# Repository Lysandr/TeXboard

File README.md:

# TeXboard
I designed a mechanical keyboard from scratch for the scientists, mathematicians, and control theorists of the world. It has LaTeX bindings for math and greek.

This also works as generic keyboard matrix interpretation code. Writtenin C-arduino for the teensy 3.1/2

12/1/2018 havent quite worked out some bugs in Latex, and functions. Excuse: I have spent maybe 2 hours on software.
2/14/2018 adding support for MkII.

Todo:
FN/GRK/LTX functions still need to be implemented (imlazy)
dual keys tend to have an odd glitch, needs to be investigated
MkIII hardware --> switch over to STM32 with QMK firmware... also put extension keys on the left, gives more mouse room. Create parametric case design, which prints perfectly and makes lasercut piece easier to deal with.

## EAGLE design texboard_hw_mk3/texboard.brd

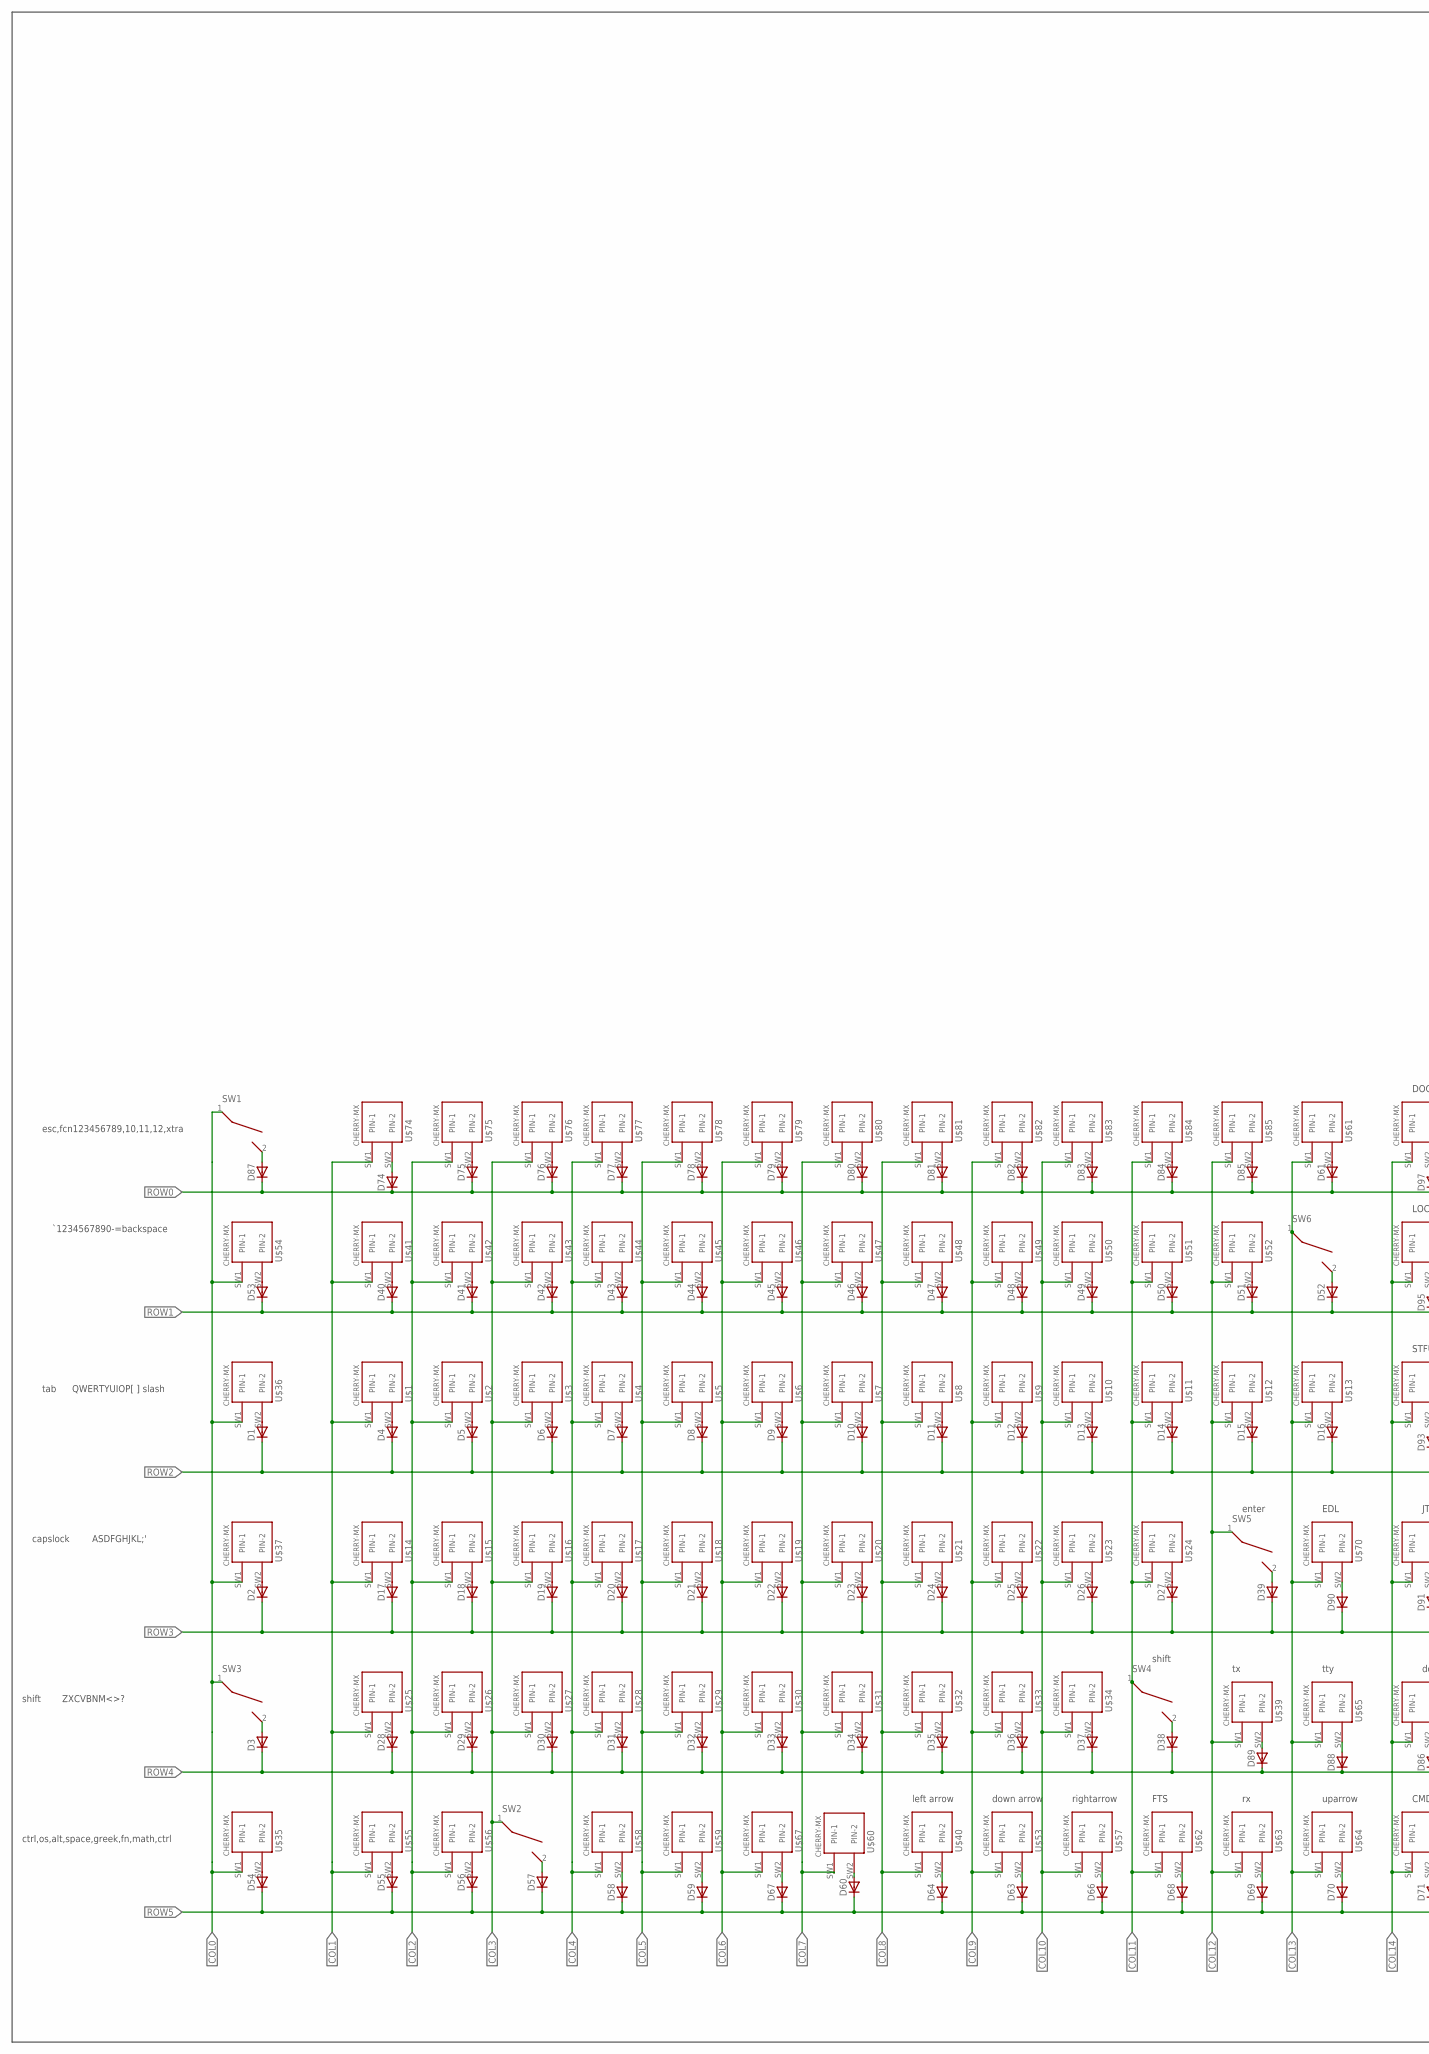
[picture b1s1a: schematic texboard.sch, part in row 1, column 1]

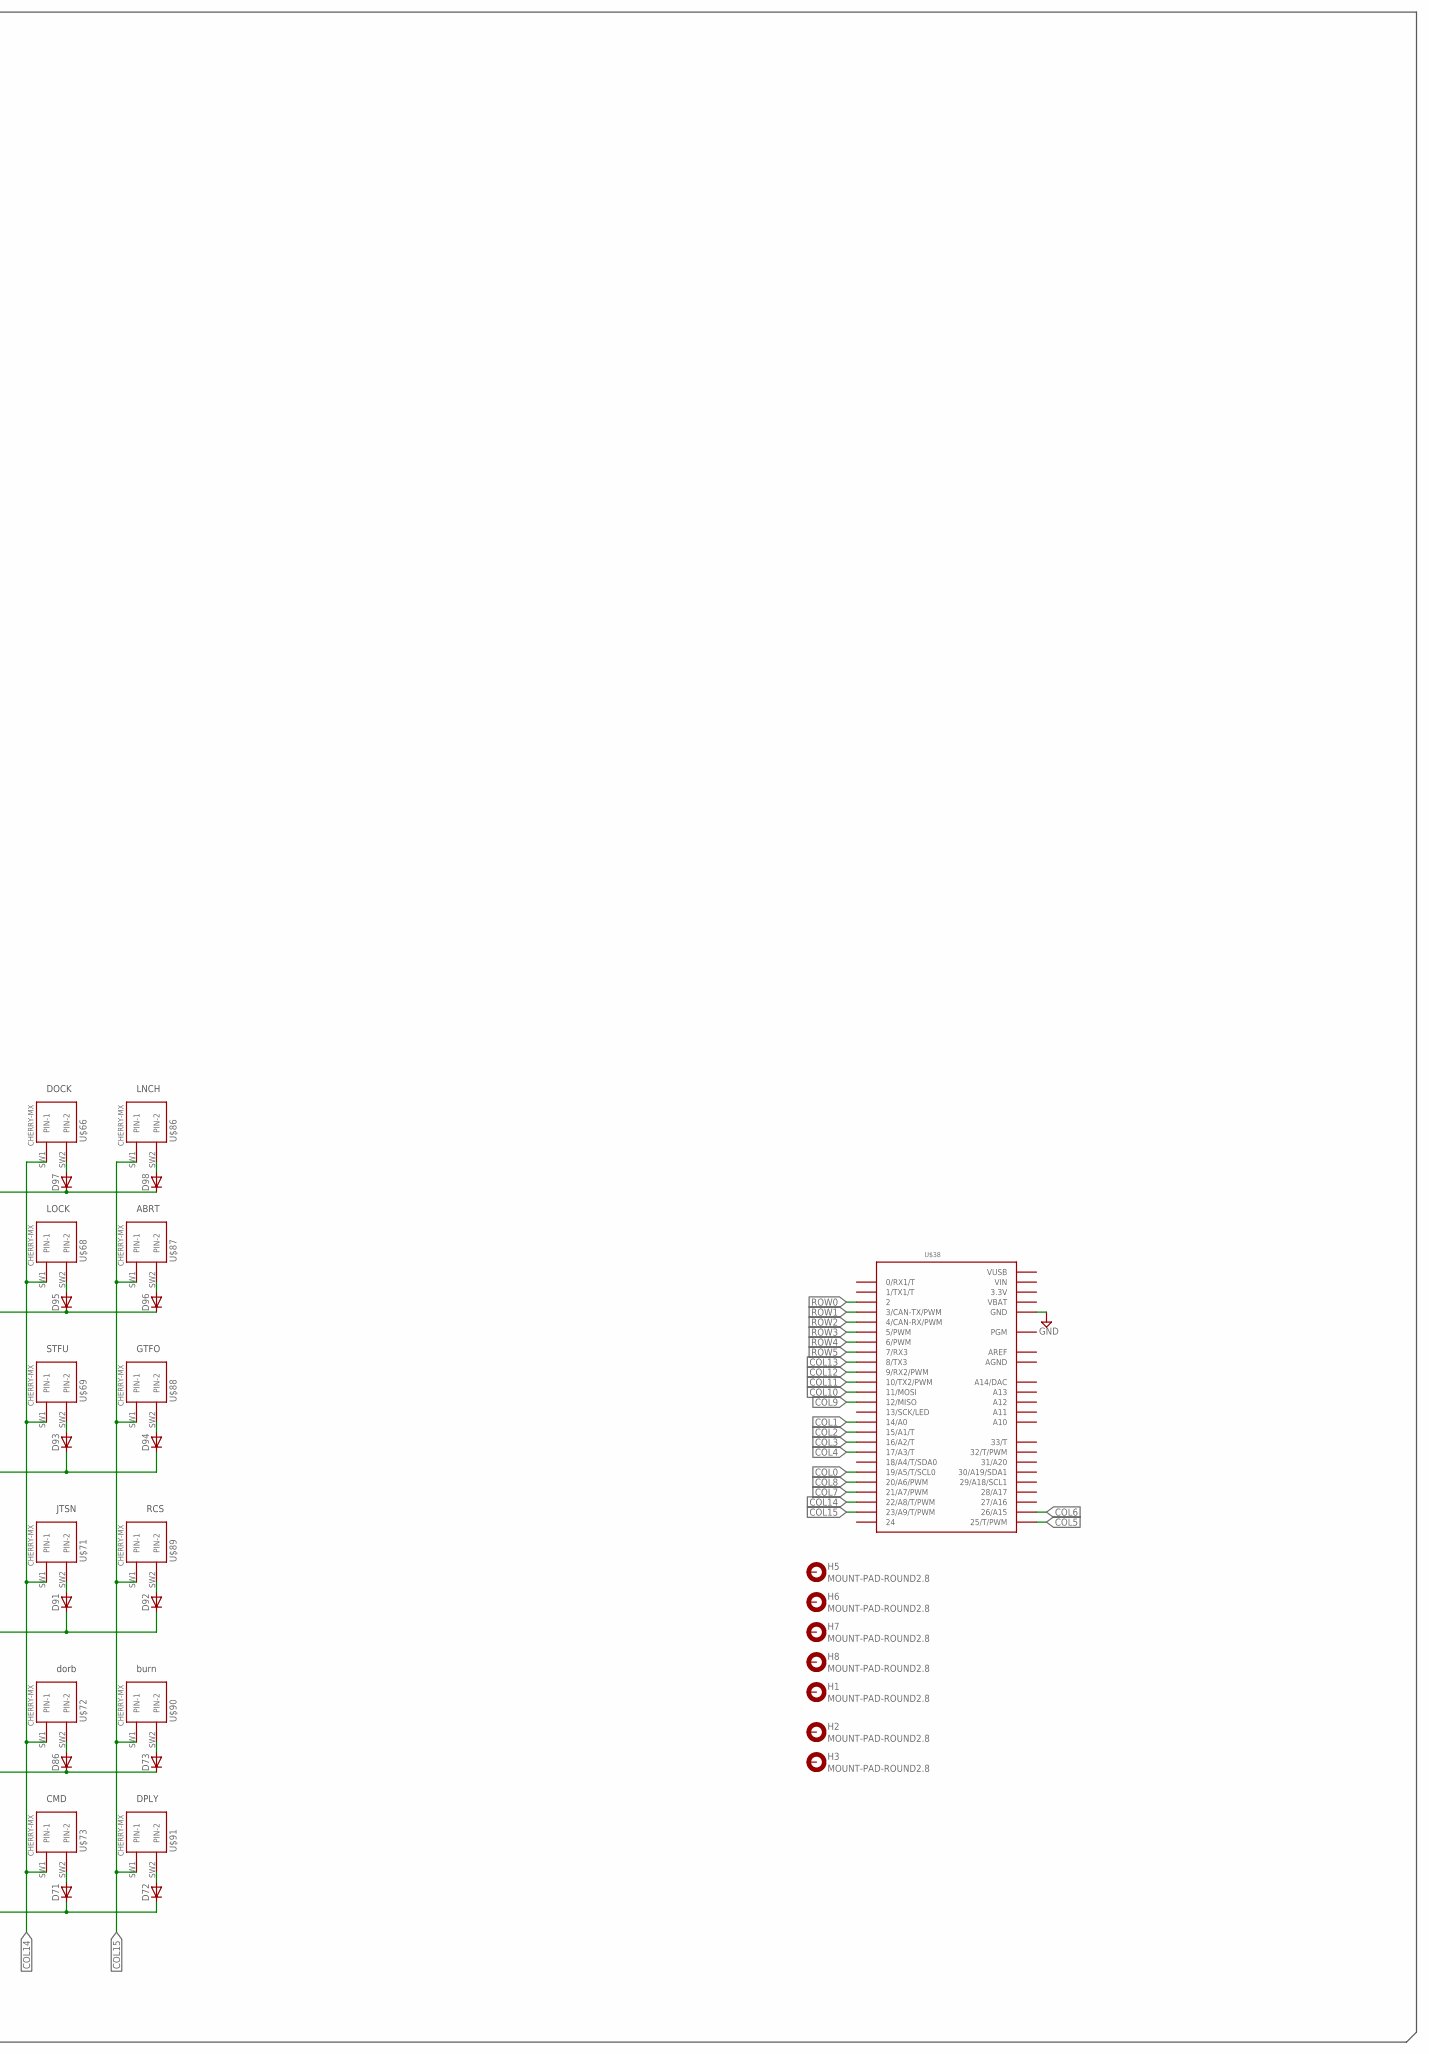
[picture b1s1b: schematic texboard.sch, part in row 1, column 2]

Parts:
D1, D2, D3, D4, D5, D6, D7, D8, D9, D10, D11, D12, D13, D14, D15, D16, D17, D18, D19, D20, D21, D22, D23, D24, D25, D26, D27, D28, D29, D30, D31, D32, D33, D34, D35, D36, D37, D38, D39, D40, D41, D42, D43, D44, D45, D46, D47, D48, D49, D50, D51, D52, D53, D54, D55, D56, D57, D58, D59, D60, D61, D63, D64, D66, D67, D68, D69, D70, D71, D72, D73, D74, D75, D76, D77, D78, D79, D80, D81, D82, D83, D84, D85, D86, D87, D88, D89, D90, D91, D92, D93, D94, D95, D96, D97, D98: DIODE_E-DO35-7; DIODE_DO35-7
H1, H2, H3, H5, H6, H7, H8: MOUNT-PAD-ROUND2.8; 2,8-PAD
SW1, SW3, SW4, SW5, SW6: CHERRY_MX_STABILIZER_2X; MX1A-XXNN_WITH_STABILIZER_2X
SW2: CHERRY_MX_WITH_FIXING_PINS_&_STABILIZER_6.25X; MX1A-XXNW_WITH_STABILIZER_6.25X
U$1, U$2, U$3, U$4, U$5, U$6, U$7, U$8, U$9, U$10, U$11, U$12, U$13, U$14, U$15, U$16, U$17, U$18, U$19, U$20, U$21, U$22, U$23, U$24, U$25, U$26, U$27, U$28, U$29, U$30, U$31, U$32, U$33, U$34, U$35, U$36, U$37, U$39, U$40, U$41, U$42, U$43, U$44, U$45, U$46, U$47, U$48, U$49, U$50, U$51, U$52, U$53, U$54, U$55, U$56, U$57, U$58, U$59, U$60, U$61, U$62, U$63, U$64, U$65, U$66, U$67, U$68, U$69, U$70, U$71, U$72, U$73, U$74, U$75, U$76, U$77, U$78, U$79, U$80, U$81, U$82, U$83, U$84, U$85, U$86, U$87, U$88, U$89, U$90, U$91: CHERRY-MX
U$38: TEENSY_3.1-3.2_ALL_PINS&PADS; TEENSY_3.0-3.2_ALL_PINS_&_PADS

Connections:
3.3V: U$38.3.3V, U$38.3.3V1 (3.3V), U$38.3.3V2 (3.3V)
AGND: U$38.AGND
AREF: U$38.AREF
COL0: SW1.1, SW3.1, U$35.SW1 (PIN-1), U$36.SW1 (PIN-1), U$37.SW1 (PIN-1), U$38.19/A5 (19/A5/T/SCL0), U$54.SW1 (PIN-1)
COL1: U$1.SW1 (PIN-1), U$14.SW1 (PIN-1), U$25.SW1 (PIN-1), U$38.14/A0, U$41.SW1 (PIN-1), U$55.SW1 (PIN-1), U$74.SW1 (PIN-1)
COL2: U$2.SW1 (PIN-1), U$15.SW1 (PIN-1), U$26.SW1 (PIN-1), U$38.15/A1 (15/A1/T), U$42.SW1 (PIN-1), U$56.SW1 (PIN-1), U$75.SW1 (PIN-1)
COL3: SW2.1, U$3.SW1 (PIN-1), U$16.SW1 (PIN-1), U$27.SW1 (PIN-1), U$38.16/A2 (16/A2/T), U$43.SW1 (PIN-1), U$76.SW1 (PIN-1)
COL4: U$4.SW1 (PIN-1), U$17.SW1 (PIN-1), U$28.SW1 (PIN-1), U$38.17/A3 (17/A3/T), U$44.SW1 (PIN-1), U$58.SW1 (PIN-1), U$77.SW1 (PIN-1)
COL5: U$5.SW1 (PIN-1), U$18.SW1 (PIN-1), U$29.SW1 (PIN-1), U$38.25 (25/T/PWM), U$45.SW1 (PIN-1), U$59.SW1 (PIN-1), U$78.SW1 (PIN-1)
COL6: U$6.SW1 (PIN-1), U$19.SW1 (PIN-1), U$30.SW1 (PIN-1), U$38.26 (26/A15), U$46.SW1 (PIN-1), U$67.SW1 (PIN-1), U$79.SW1 (PIN-1)
COL7: U$7.SW1 (PIN-1), U$20.SW1 (PIN-1), U$31.SW1 (PIN-1), U$38.21/A7 (21/A7/PWM), U$47.SW1 (PIN-1), U$60.SW1 (PIN-1), U$80.SW1 (PIN-1)
COL8: U$8.SW1 (PIN-1), U$21.SW1 (PIN-1), U$32.SW1 (PIN-1), U$38.20/A6 (20/A6/PWM), U$40.SW1 (PIN-1), U$48.SW1 (PIN-1), U$81.SW1 (PIN-1)
COL9: U$9.SW1 (PIN-1), U$22.SW1 (PIN-1), U$33.SW1 (PIN-1), U$38.12 (12/MISO), U$49.SW1 (PIN-1), U$53.SW1 (PIN-1), U$82.SW1 (PIN-1)
COL10: U$10.SW1 (PIN-1), U$23.SW1 (PIN-1), U$34.SW1 (PIN-1), U$38.11 (11/MOSI), U$50.SW1 (PIN-1), U$57.SW1 (PIN-1), U$83.SW1 (PIN-1)
COL11: SW4.1, U$11.SW1 (PIN-1), U$24.SW1 (PIN-1), U$38.10 (10/TX2/PWM), U$51.SW1 (PIN-1), U$62.SW1 (PIN-1), U$84.SW1 (PIN-1)
COL12: SW5.1, U$12.SW1 (PIN-1), U$38.9 (9/RX2/PWM), U$39.SW1 (PIN-1), U$52.SW1 (PIN-1), U$63.SW1 (PIN-1), U$85.SW1 (PIN-1)
COL13: SW6.1, U$13.SW1 (PIN-1), U$38.8 (8/TX3), U$61.SW1 (PIN-1), U$64.SW1 (PIN-1), U$65.SW1 (PIN-1), U$70.SW1 (PIN-1)
COL14: U$38.22/A8 (22/A8/T/PWM), U$66.SW1 (PIN-1), U$68.SW1 (PIN-1), U$69.SW1 (PIN-1), U$71.SW1 (PIN-1), U$72.SW1 (PIN-1), U$73.SW1 (PIN-1)
COL15: U$38.23/A9 (23/A9/T/PWM), U$86.SW1 (PIN-1), U$87.SW1 (PIN-1), U$88.SW1 (PIN-1), U$89.SW1 (PIN-1), U$90.SW1 (PIN-1), U$91.SW1 (PIN-1)
GND: U$38.GND, U$38.GND1 (GND), U$38.GND2 (GND)
unnamed: D4.A (C), U$1.SW2 (PIN-2)
unnamed: D5.A (C), U$2.SW2 (PIN-2)
unnamed: D6.A (C), U$3.SW2 (PIN-2)
unnamed: D7.A (C), U$4.SW2 (PIN-2)
unnamed: D8.A (C), U$5.SW2 (PIN-2)
unnamed: D9.A (C), U$6.SW2 (PIN-2)
unnamed: D10.A (C), U$7.SW2 (PIN-2)
unnamed: D11.A (C), U$8.SW2 (PIN-2)
unnamed: D12.A (C), U$9.SW2 (PIN-2)
unnamed: D13.A (C), U$10.SW2 (PIN-2)
unnamed: D14.A (C), U$11.SW2 (PIN-2)
unnamed: D15.A (C), U$12.SW2 (PIN-2)
unnamed: D16.A (C), U$13.SW2 (PIN-2)
unnamed: D17.A (C), U$14.SW2 (PIN-2)
unnamed: D18.A (C), U$15.SW2 (PIN-2)
unnamed: D19.A (C), U$16.SW2 (PIN-2)
unnamed: D20.A (C), U$17.SW2 (PIN-2)
unnamed: D21.A (C), U$18.SW2 (PIN-2)
unnamed: D22.A (C), U$19.SW2 (PIN-2)
unnamed: D23.A (C), U$20.SW2 (PIN-2)
unnamed: D24.A (C), U$21.SW2 (PIN-2)
unnamed: D25.A (C), U$22.SW2 (PIN-2)
unnamed: D26.A (C), U$23.SW2 (PIN-2)
unnamed: D27.A (C), U$24.SW2 (PIN-2)
unnamed: D28.A (C), U$25.SW2 (PIN-2)
unnamed: D29.A (C), U$26.SW2 (PIN-2)
unnamed: D30.A (C), U$27.SW2 (PIN-2)
unnamed: D31.A (C), U$28.SW2 (PIN-2)
unnamed: D32.A (C), U$29.SW2 (PIN-2)
unnamed: D33.A (C), U$30.SW2 (PIN-2)
unnamed: D34.A (C), U$31.SW2 (PIN-2)
unnamed: D35.A (C), U$32.SW2 (PIN-2)
unnamed: D36.A (C), U$33.SW2 (PIN-2)
unnamed: D37.A (C), U$34.SW2 (PIN-2)
unnamed: D60.A (C), U$60.SW2 (PIN-2)
unnamed: D61.A (C), U$61.SW2 (PIN-2)
unnamed: D57.A (C), SW2.2
unnamed: D97.A (C), U$66.SW2 (PIN-2)
unnamed: D67.A (C), U$67.SW2 (PIN-2)
unnamed: D98.A (C), U$86.SW2 (PIN-2)
unnamed: D87.A (C), SW1.2
unnamed: D69.A (C), U$63.SW2 (PIN-2)
unnamed: D68.A (C), U$62.SW2 (PIN-2)
unnamed: D66.A (C), U$57.SW2 (PIN-2)
unnamed: D63.A (C), U$53.SW2 (PIN-2)
unnamed: D64.A (C), U$40.SW2 (PIN-2)
unnamed: D1.A (C), U$36.SW2 (PIN-2)
unnamed: D2.A (C), U$37.SW2 (PIN-2)
unnamed: D3.A (C), SW3.2
unnamed: D38.A (C), SW4.2
unnamed: D39.A (C), SW5.2
unnamed: D40.A (C), U$41.SW2 (PIN-2)
unnamed: D41.A (C), U$42.SW2 (PIN-2)
unnamed: D42.A (C), U$43.SW2 (PIN-2)
unnamed: D43.A (C), U$44.SW2 (PIN-2)
unnamed: D44.A (C), U$45.SW2 (PIN-2)
unnamed: D45.A (C), U$46.SW2 (PIN-2)
unnamed: D46.A (C), U$47.SW2 (PIN-2)
unnamed: D47.A (C), U$48.SW2 (PIN-2)
unnamed: D48.A (C), U$49.SW2 (PIN-2)
unnamed: D49.A (C), U$50.SW2 (PIN-2)
unnamed: D50.A (C), U$51.SW2 (PIN-2)
unnamed: D51.A (C), U$52.SW2 (PIN-2)
unnamed: D52.A (C), SW6.2
unnamed: D54.A (C), U$35.SW2 (PIN-2)
unnamed: D55.A (C), U$55.SW2 (PIN-2)
unnamed: D56.A (C), U$56.SW2 (PIN-2)
unnamed: D70.A (C), U$64.SW2 (PIN-2)
unnamed: D58.A (C), U$58.SW2 (PIN-2)
unnamed: D59.A (C), U$59.SW2 (PIN-2)
unnamed: D71.A (C), U$73.SW2 (PIN-2)
unnamed: D72.A (C), U$91.SW2 (PIN-2)
unnamed: D89.A (C), U$39.SW2 (PIN-2)
unnamed: D88.A (C), U$65.SW2 (PIN-2)
unnamed: D86.A (C), U$72.SW2 (PIN-2)
unnamed: D73.A (C), U$90.SW2 (PIN-2)
unnamed: D91.A (C), U$71.SW2 (PIN-2)
unnamed: D53.A (C), U$54.SW2 (PIN-2)
unnamed: D92.A (C), U$89.SW2 (PIN-2)
unnamed: D90.A (C), U$70.SW2 (PIN-2)
unnamed: D94.A (C), U$88.SW2 (PIN-2)
unnamed: D93.A (C), U$69.SW2 (PIN-2)
unnamed: D95.A (C), U$68.SW2 (PIN-2)
unnamed: D96.A (C), U$87.SW2 (PIN-2)
unnamed: D74.A (C), U$74.SW2 (PIN-2)
unnamed: D75.A (C), U$75.SW2 (PIN-2)
unnamed: D76.A (C), U$76.SW2 (PIN-2)
unnamed: D77.A (C), U$77.SW2 (PIN-2)
unnamed: D78.A (C), U$78.SW2 (PIN-2)
unnamed: D79.A (C), U$79.SW2 (PIN-2)
unnamed: D80.A (C), U$80.SW2 (PIN-2)
unnamed: D81.A (C), U$81.SW2 (PIN-2)
unnamed: D82.A (C), U$82.SW2 (PIN-2)
unnamed: D83.A (C), U$83.SW2 (PIN-2)
unnamed: D84.A (C), U$84.SW2 (PIN-2)
unnamed: D85.A (C), U$85.SW2 (PIN-2)
ROW0: D61.C (A), D74.C (A), D75.C (A), D76.C (A), D77.C (A), D78.C (A), D79.C (A), D80.C (A), D81.C (A), D82.C (A), D83.C (A), D84.C (A), D85.C (A), D87.C (A), D97.C (A), D98.C (A), U$38.2
ROW1: D40.C (A), D41.C (A), D42.C (A), D43.C (A), D44.C (A), D45.C (A), D46.C (A), D47.C (A), D48.C (A), D49.C (A), D50.C (A), D51.C (A), D52.C (A), D53.C (A), D95.C (A), D96.C (A), U$38.3 (3/CAN-TX/PWM)
ROW2: D1.C (A), D4.C (A), D5.C (A), D6.C (A), D7.C (A), D8.C (A), D9.C (A), D10.C (A), D11.C (A), D12.C (A), D13.C (A), D14.C (A), D15.C (A), D16.C (A), D93.C (A), D94.C (A), U$38.4 (4/CAN-RX/PWM)
ROW3: D2.C (A), D17.C (A), D18.C (A), D19.C (A), D20.C (A), D21.C (A), D22.C (A), D23.C (A), D24.C (A), D25.C (A), D26.C (A), D27.C (A), D39.C (A), D90.C (A), D91.C (A), D92.C (A), U$38.5 (5/PWM)
ROW4: D3.C (A), D28.C (A), D29.C (A), D30.C (A), D31.C (A), D32.C (A), D33.C (A), D34.C (A), D35.C (A), D36.C (A), D37.C (A), D38.C (A), D73.C (A), D86.C (A), D88.C (A), D89.C (A), U$38.6 (6/PWM)
ROW5: D54.C (A), D55.C (A), D56.C (A), D57.C (A), D58.C (A), D59.C (A), D60.C (A), D63.C (A), D64.C (A), D66.C (A), D67.C (A), D68.C (A), D69.C (A), D70.C (A), D71.C (A), D72.C (A), U$38.7 (7/RX3)
VBAT: U$38.VBAT
VIN: U$38.VIN
VUSB: U$38.VUSB

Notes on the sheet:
QWERTYUIOP[ ] slash
ASDFGHJKL;'
ZXCVBNM<>?
shift
capslock
tab
enter
`1234567890-=backspace
ctrl,os,alt,space,greek,fn,math,ctrl
esc,fcn123456789,10,11,12,xtra
left arrow
down arrow
rightarrow
FTS
DPLY
CMD
uparrow
tty
dorb
burn
EDL
JTSN
RCS
STFU
GTFO
LOCK
ABRT
DOCK
LNCH

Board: 2 copper layers, 200 parts (6 on the bottom side), 120 nets, no tracks yet.

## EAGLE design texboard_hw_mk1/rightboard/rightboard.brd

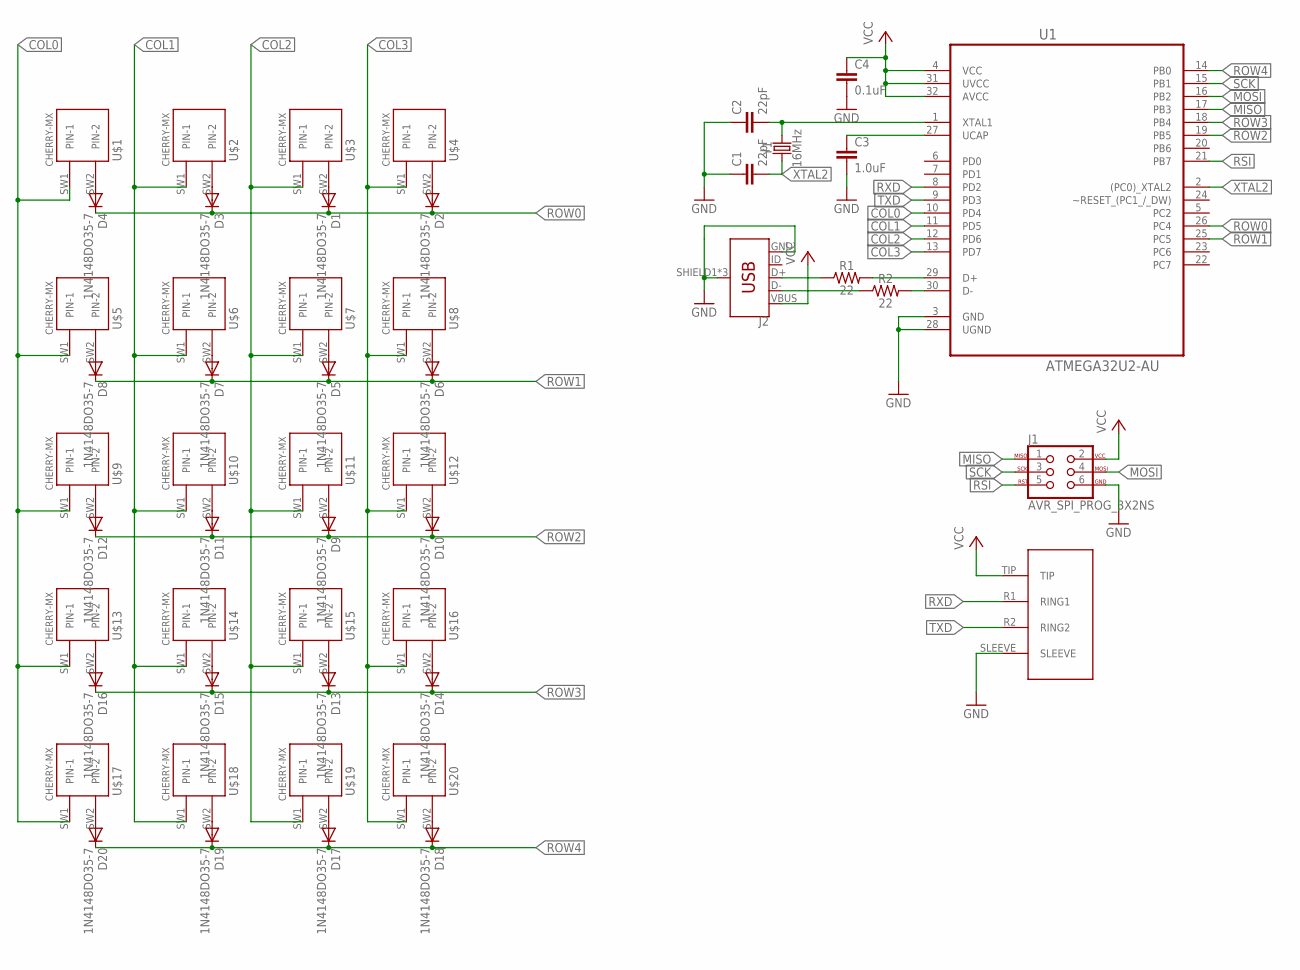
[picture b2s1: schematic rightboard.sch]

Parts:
C1, C2: 22pF; 0603
C3: 1.0uF; 0603
C4: 0.1uF; 0603
D1, D2, D3, D4, D5, D6, D7, D8, D9, D10, D11, D12, D13, D14, D15, D16, D17, D18, D19, D20: 1N4148DO35-7; DO35-7
J1: AVR_SPI_PROG_3X2NS; 2X3-NS
J2: USB_MICRO-B_FEMALE-SMT; USB-B-MICRO-SMD
R1, R2: 22; 0603
U1: ATMEGA32U2-AU; QFP80P900X900X120-32N
U$1, U$2, U$3, U$4, U$5, U$6, U$7, U$8, U$9, U$10, U$11, U$12, U$13, U$14, U$15, U$16, U$17, U$18, U$19, U$20: CHERRY-MX
U$21: 54-00035
Y1: 16MHz; HC49US

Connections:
COL0: U1.10 (PD4), U$1.SW1 (PIN-1), U$5.SW1 (PIN-1), U$9.SW1 (PIN-1), U$13.SW1 (PIN-1), U$17.SW1 (PIN-1)
COL1: U1.11 (PD5), U$2.SW1 (PIN-1), U$6.SW1 (PIN-1), U$10.SW1 (PIN-1), U$14.SW1 (PIN-1), U$18.SW1 (PIN-1)
COL2: U1.12 (PD6), U$3.SW1 (PIN-1), U$7.SW1 (PIN-1), U$11.SW1 (PIN-1), U$15.SW1 (PIN-1), U$19.SW1 (PIN-1)
COL3: U1.13 (PD7), U$4.SW1 (PIN-1), U$8.SW1 (PIN-1), U$12.SW1 (PIN-1), U$16.SW1 (PIN-1), U$20.SW1 (PIN-1)
GND: C1.1, C2.1, C3.2, C4.2, J1.6, J2.GND, J2.SHIELD1 (SHIELD), J2.SHIELD2 (SHIELD), J2.SHIELD3 (SHIELD), U1.3 (GND), U1.28 (UGND), U$21.SLEEVE
MISO: J1.1, U1.17 (PB3)
MOSI: J1.4, U1.16 (PB2)
unnamed: D1.A, U$3.SW2 (PIN-2)
unnamed: D2.A, U$4.SW2 (PIN-2)
unnamed: D3.A, U$2.SW2 (PIN-2)
unnamed: D4.A, U$1.SW2 (PIN-2)
unnamed: D5.A, U$7.SW2 (PIN-2)
unnamed: D6.A, U$8.SW2 (PIN-2)
unnamed: D7.A, U$6.SW2 (PIN-2)
unnamed: D8.A, U$5.SW2 (PIN-2)
unnamed: D9.A, U$11.SW2 (PIN-2)
unnamed: D10.A, U$12.SW2 (PIN-2)
unnamed: D11.A, U$10.SW2 (PIN-2)
unnamed: D12.A, U$9.SW2 (PIN-2)
unnamed: D13.A, U$15.SW2 (PIN-2)
unnamed: D14.A, U$16.SW2 (PIN-2)
unnamed: D15.A, U$14.SW2 (PIN-2)
unnamed: D16.A, U$13.SW2 (PIN-2)
unnamed: D17.A, U$19.SW2 (PIN-2)
unnamed: D18.A, U$20.SW2 (PIN-2)
unnamed: D19.A, U$18.SW2 (PIN-2)
unnamed: D20.A, U$17.SW2 (PIN-2)
unnamed: C2.2, U1.1 (XTAL1), Y1.2
unnamed: R1.2, U1.29 (D+)
unnamed: J2.D+, R1.1
unnamed: J2.D-, R2.1
unnamed: R2.2, U1.30 (D-)
unnamed: C3.1, U1.27 (UCAP)
ROW0: D1.C, D2.C, D3.C, D4.C, U1.26 (PC4)
ROW1: D5.C, D6.C, D7.C, D8.C, U1.25 (PC5)
ROW2: D9.C, D10.C, D11.C, D12.C, U1.19 (PB5)
ROW3: D13.C, D14.C, D15.C, D16.C, U1.18 (PB4)
ROW4: D17.C, D18.C, D19.C, D20.C, U1.14 (PB0)
RSI: J1.5, U1.21 (PB7)
RXD: U1.8 (PD2), U$21.R1 (RING1)
SCK: J1.3, U1.15 (PB1)
TXD: U1.9 (PD3), U$21.R2 (RING2)
VCC: C4.1, J1.2, J2.VBUS, U1.4 (VCC), U1.31 (UVCC), U1.32 (AVCC), U$21.TIP
XTAL2: C1.2, U1.2 ((PC0)_XTAL2), Y1.1

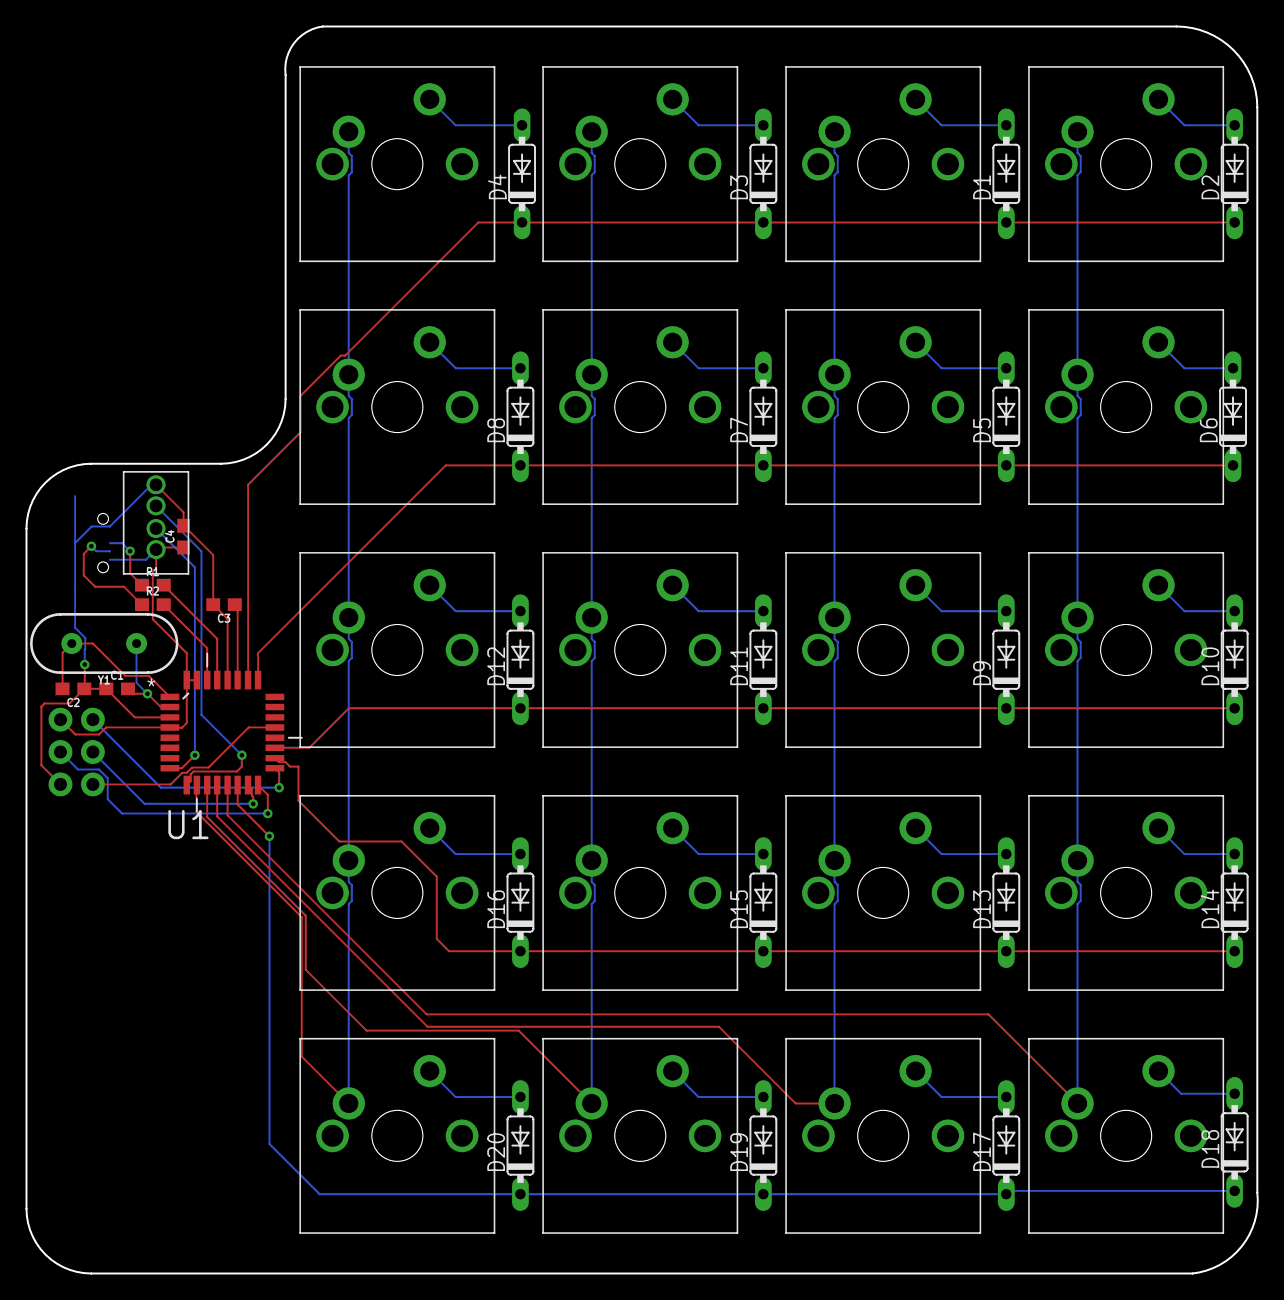
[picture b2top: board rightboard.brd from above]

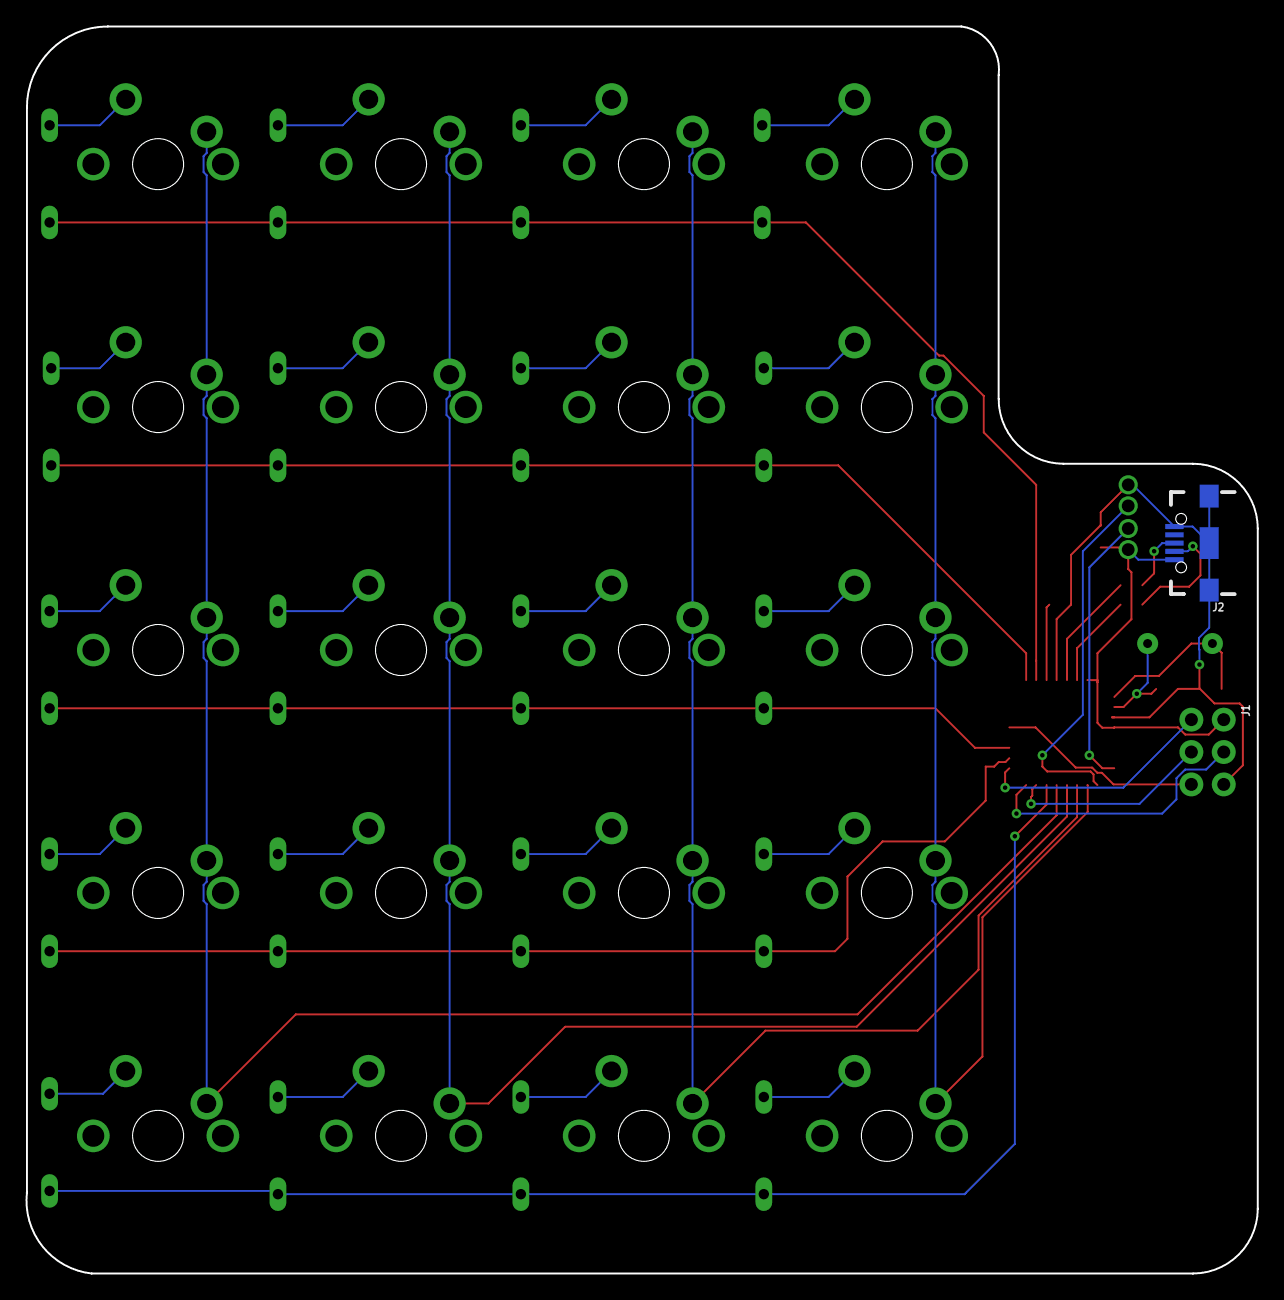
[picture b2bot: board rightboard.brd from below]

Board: 2 copper layers, 96.6 x 97.8 mm, 51 parts (2 on the bottom side), 44 nets.

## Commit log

2018-12-01 adding hardware and software
2019-02-12 added mkII
2019-02-12 fixed some shit maybe idk
2019-10-06 asdf
2019-10-26 adding dxf fuckery
2020-07-26 adding texbrd mkII stuff
2020-09-21 whatever new shit i added

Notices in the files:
parts and their libraries:
SparkFun-Connectors: Licensing: Creative Commons ShareAlike 4.0 International - https://creativecommons.org/licenses/by-sa/4.0
